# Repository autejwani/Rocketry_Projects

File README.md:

# Rocketry Projects

A collection of my model rocketry projects including flight computer hardware, firmware, ground station software, and certification flight documentation.

---

## Projects

| Project | Status | Current Checkpoint | Description |
|---|---|---|---|
| TALON-1 | In Progress | TALON-1B and 1C complete, TALON-1A schematic in progress | Modular 3-board flight computer system |
| Ground Station | In Progress | 3D orientation view complete, LoRa and GPS support planned | Python telemetry ground station application |
| Flight Computer | Complete | Ground station validation complete | First iteration STM32F411RE flight computer |
| Telemetry | Complete | Validated on STM32F411RE, TALON-1 port planned | C++ telemetry protocol for STM32 |
| LoRa Test | Planned | Not started | LoRa radio range and reliability testing |
| L1 | Complete | Certified March 8 2025 at Higgs Farm | H100 motor, Tripoli L1 certification |
| L2 | In Progress | CAD in progress | J, K, or L class dual deploy certification flight |
| L3 | Planned | Not started | M class or higher dual deploy certification flight |

---

## TALON-1 System Overview

TALON-1 is a modular flight computer built around a 3-board stacking architecture connected via 2.54mm pitch pin headers. Each board serves a dedicated purpose and can be developed and tested independently.

**Base Layer — TALON-1A**
- STM32H503KBU6 microcontroller
- AP63203WU-7 3.3V 2A buck converter
- TB6612FNG dual H-bridge motor driver for airbrake control
- Distributes power and signals to upper boards via stacking headers

**Sensor Layer — TALON-1B**
- IMU: LSM6DSVTR — accelerometer and gyroscope
- Barometer: LPS27HHWTR — pressure and temperature
- Magnetometer: IIS2MDCTR

**Communications Layer — TALON-1C**
- GPS: MAX-M10M-00B
- LoRa: RA-01H — 915 MHz long range telemetry

---

## Flight Computer (First Iteration)

The original flight computer used for development and testing. Built around the STM32F411RE Nucleo development board.

**Sensors**
- IMU: LSM6DSO — accelerometer and gyroscope
- Barometer: LPS22HB — pressure and temperature

This board was used to develop and validate the telemetry protocol, sensor libraries, and ground station application before designing the TALON-1 custom PCB.

---

## Ground Station

A desktop application written in Python that receives and displays live telemetry from any flight computer that implements the TALON-1 packet protocol.

**Features**
- Serial port and baud rate selection
- Live barometer readout — pressure, temperature, altitude
- Live accelerometer and gyroscope readouts
- Flight state display with progress indicator across all flight phases
- 3D rocket orientation visualization driven by live gyroscope data
- Compatible with any future flight computer that implements the telemetry protocol

---

## Telemetry Protocol

All flight computers in this repository share a common binary packet format transmitted over UART at 115200 baud. The protocol is transport independent — the same packet format works over USB serial today and will work over LoRa radio in future revisions.

| Parameter | Value |
|---|---|
| Header bytes | 0x07 0x32 |
| Packet size | 44 bytes |
| Byte order | Little endian |
| Checksum | XOR of all bytes between header and checksum field |
| Data rate | 20 Hz |

Any flight computer that implements this protocol is immediately compatible with the ground station without any changes to the application. See `Telemetry/README.md` for the full packet specification.

---

## Flight Certifications

| Level | Date | Location | Motor | Status |
|---|---|---|---|---|
| L1 | March 8, 2025 | Higgs Farm | H100 | Complete |
| L2 | TBD | TBD | J, K, or L class | In Progress |
| L3 | TBD | TBD | M class or higher | Planned |

---

## Repository Structure
```
Rocketry_Projects/
│
├── TALON-1/              modular flight computer hardware and firmware
├── Ground Station/       Python telemetry ground station application
├── Flight Computer/      first iteration flight computer
├── Telemetry/            shared C++ telemetry protocol
├── LoRa_Test/            LoRa radio testing
├── L1/                   level 1 certification flight
├── L2/                   level 2 certification flight
└── L3/                   level 3 certification flight
```

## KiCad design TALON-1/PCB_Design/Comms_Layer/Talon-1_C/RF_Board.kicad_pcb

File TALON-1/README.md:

# TALON-1 Modular Flight Computer System

TALON-1 is a modular three-board avionics stack designed for high-powered rocketry applications across all certification levels under Tripoli Rocketry Association and National Association of Rocketry guidelines. The system operates in the 915 MHz ISM band for long range telemetry.

---

## Development Checkpoints

| Checkpoint | TALON-1A | TALON-1B | TALON-1C |
|---|---|---|---|
| Component Selection | Complete | Complete | Complete |
| Schematic Design | Complete | Complete | Complete |
| PCB Layout | Complete | Complete | Complete |
| PCB Fabrication | Not Started | Not Started | Not Started |
| Assembly | Not Started | Not Started | Not Started |
| Bring-up Testing | Not Started | Not Started | Not Started |
| Sensor Validation | Not Started | Not Started | Not Started |
| System Integration | Not Started | Not Started | Not Started |
| Flight Testing | Not Started | Not Started | Not Started |

---

## System Overview

The TALON-1 is a three-board modular avionics stack built on a circular PCB form factor. The three modules are designated TALON-1A (Core Processing), TALON-1B (Sensing), and TALON-1C (RF and Navigation), stacked bottom to top and connected via 2.54mm pitch pin headers.

---

## Assembled Stack

*Photo of fully assembled TALON-1 stack (all three boards) to be added here.*

*CAD render of assembled stack to be added here.*

---

## Board Overview

### TALON-1A — Core Processing Module
*PCB image to be added here.*

The base board of the stack. Hosts the STM32H503KBU6 microcontroller running at up to 250 MHz on an ARM Cortex-M33 core, the AP63203WU-7 3.3V 2A buck converter, and the TB6612FNG dual H-bridge motor driver for airbrake control. All inter-board signals originate from this board via male 2.54mm pin headers.

| Item | Detail |
|---|---|
| Microcontroller | STM32H503KBU6 |
| Core | ARM Cortex-M33 @ 250 MHz |
| Flash | 128 KB |
| SRAM | 32 KB |
| Package | UFQFPN-32 |
| Power Regulator | AP63203WU-7 — 3.3V 2A |
| Motor Driver | TB6612FNG — Dual H-Bridge |
| Input Voltage | 3S LiPo (11.1V nominal, 12.6V max) |

---

### TALON-1B — Sensing Module
*PCB image to be added here.*

The middle board of the stack. Carries three ST MEMS sensors on a shared I2C bus. Receives signals from TALON-1A below and passes all signals through to TALON-1C above.

| Sensor | Part | Function | Interface | Address |
|---|---|---|---|---|
| IMU | LSM6DSVTR | 3-axis Accel + 3-axis Gyro | I2C | 0x6A or 0x6B |
| Barometer | LPS27HHWTR | Pressure + Temperature | I2C | 0x5C or 0x5D |
| Magnetometer | IIS2MDCTR | 3-axis Magnetic Field | I2C | 0x1E (fixed) |

I2C pull-up resistors (4.7kΩ) are placed on this board only. No additional pull-ups on TALON-1A or TALON-1C to avoid bus loading.

---

### TALON-1C — RF and Navigation Module
*PCB image to be added here.*

The topmost board of the stack. Hosts the RA-01H 915 MHz LoRa transceiver and the u-blox MAX-M10M GNSS receiver. Being at the top of the stack positions this board closest to any externally mounted antenna, minimising RF feedline losses.

| Device | Part | Function | Interface | Address / Notes |
|---|---|---|---|---|
| LoRa Radio | RA-01H | 915 MHz Telemetry | SPI | CS, DIO1, RESET |
| GNSS | MAX-M10M-00B | GPS, GLONASS, Galileo, BeiDou | I2C | 0x42 (fixed) |

The RA-01H uses a quarter-wave whip antenna at 915 MHz with a wire length of approximately 81.9 mm. The MAX-M10M connects to a separate GNSS antenna via SMA connector.

---

## Inter-Board Bus Pinout

| Signal | Type | Destination |
|---|---|---|
| 3V3 | Power | All boards |
| GND | Power | All boards |
| SDA | I2C Data | TALON-1B sensors, TALON-1C GPS |
| SCL | I2C Clock | TALON-1B sensors, TALON-1C GPS |
| MOSI | SPI Data | TALON-1C RA-01H |
| MISO | SPI Data | TALON-1C RA-01H |
| SCK | SPI Clock | TALON-1C RA-01H |
| CS | SPI Chip Select | TALON-1C RA-01H |
| DIO1 | Digital Input | TALON-1C RA-01H interrupt |
| RESET | Digital Output | TALON-1C RA-01H reset |

---

## Power Architecture

The entire stack is powered by a single 3S LiPo battery (11.1V nominal, 12.6V fully charged). The AP63203WU-7 buck converter on TALON-1A regulates this down to 3.3V for all digital logic and sensors across the stack. Raw battery voltage is fed directly to the TB6612FNG motor driver for airbrake motor control.

---

## Firmware

Firmware targets the STM32H503KBU6 using the STM32 HAL library via PlatformIO. Development is ongoing and will cover sensor acquisition, flight state machine logic, telemetry transmission over LoRa, and GNSS data parsing. See the `Code/` folder for current firmware.

---

## Repository Structure
```
TALON-1/
│
├── PCB Design/
│   ├── Base Layer/        TALON-1A KiCad files
│   ├── Sensor Layer/      TALON-1B KiCad files
│   └── Comms Layer/       TALON-1C KiCad files
│
├── CAD/                   mechanical CAD files
├── Code/                  PlatformIO firmware project
│
└── Docs/
    ├── architecture.md
    ├── packet_protocol.md
    └── board_pinout.md
```

---

## Design Philosophy

TALON-1 was designed with an emphasis on modularity, repairability, and iterative development. Separating processing, sensing, and RF functions into discrete modules means a change to one layer does not require a redesign of the others. Each board can be developed, tested, and replaced independently.

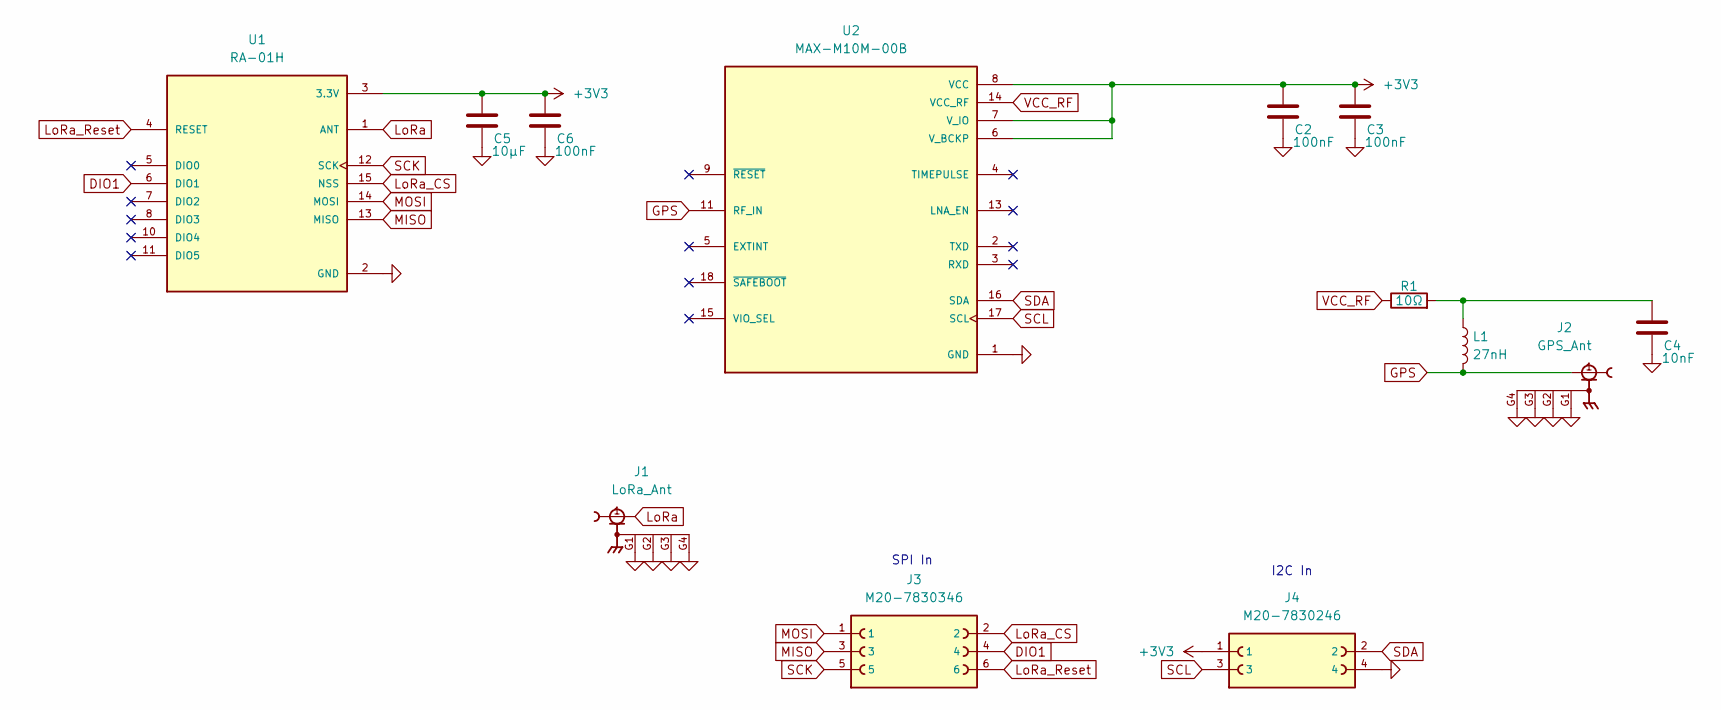
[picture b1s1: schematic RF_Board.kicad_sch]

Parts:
C2, C3, C6: 100nF; C_0805_2012Metric
C4: 10nF; C_0805_2012Metric
C5: 10µF; C_0805_2012Metric
J1: LoRa_Ant; GRADCONN_RFPC-SMA28-F; PARTREV 1.0; DigiKey_Part_Number 2073-RFPC-SMA28-F-ND
J2: GPS_Ant; GRADCONN_RFPC-SMA28-F; PARTREV 1.0; DigiKey_Part_Number 2073-RFPC-SMA28-F-ND
J3: M20-7830346; HARWIN_M20-7830346; DigiKey_Part_Number 952-1781-ND
J4: M20-7830246; HARWIN_M20-7830246; PARTREV 13; DigiKey_Part_Number 952-2147-ND
L1: 27nH; L_0805_2012Metric
R1: 10Ω; R_0603_1608Metric
U1: RA-01H; XCVR_RA-01H; PARTREV V1.0
U2: MAX-M10M-00B; XCVR_MAX-M10M-00B; PARTREV C1; DigiKey_Part_Number 672-MAX-M10M-00BCT-ND

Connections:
+3V3: C2.1, C3.1, C5.1, C6.1, J4.1, U1.3 (3.3V), U2.6 (V_BCKP), U2.7 (V_IO), U2.8 (VCC)
DIO1: J3.4, U1.6 (DIO1)
GND: C2.2, C3.2, C4.2, C5.2, C6.2, J1.G1, J1.G2, J1.G3, J1.G4, J2.G1, J2.G2, J2.G3, J2.G4, J4.4, U1.2 (GND), U1.9 (GND), U1.16 (GND), U2.1 (GND), U2.10 (GND), U2.12 (GND)
GPS: J2.1, L1.2, U2.11 (RF_IN)
LoRa: J1.1, U1.1 (ANT)
LoRa_CS: J3.2, U1.15 (NSS)
LoRa_Reset: J3.6, U1.4 (RESET)
MISO: J3.3, U1.13 (MISO)
MOSI: J3.1, U1.14 (MOSI)
unnamed: C4.1, L1.1, R1.2
SCK: J3.5, U1.12 (SCK)
SCL: J4.3, U2.17 (SCL)
SDA: J4.2, U2.16 (SDA)
VCC_RF: R1.1, U2.14 (VCC_RF)

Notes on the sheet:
SPI In
I2C In

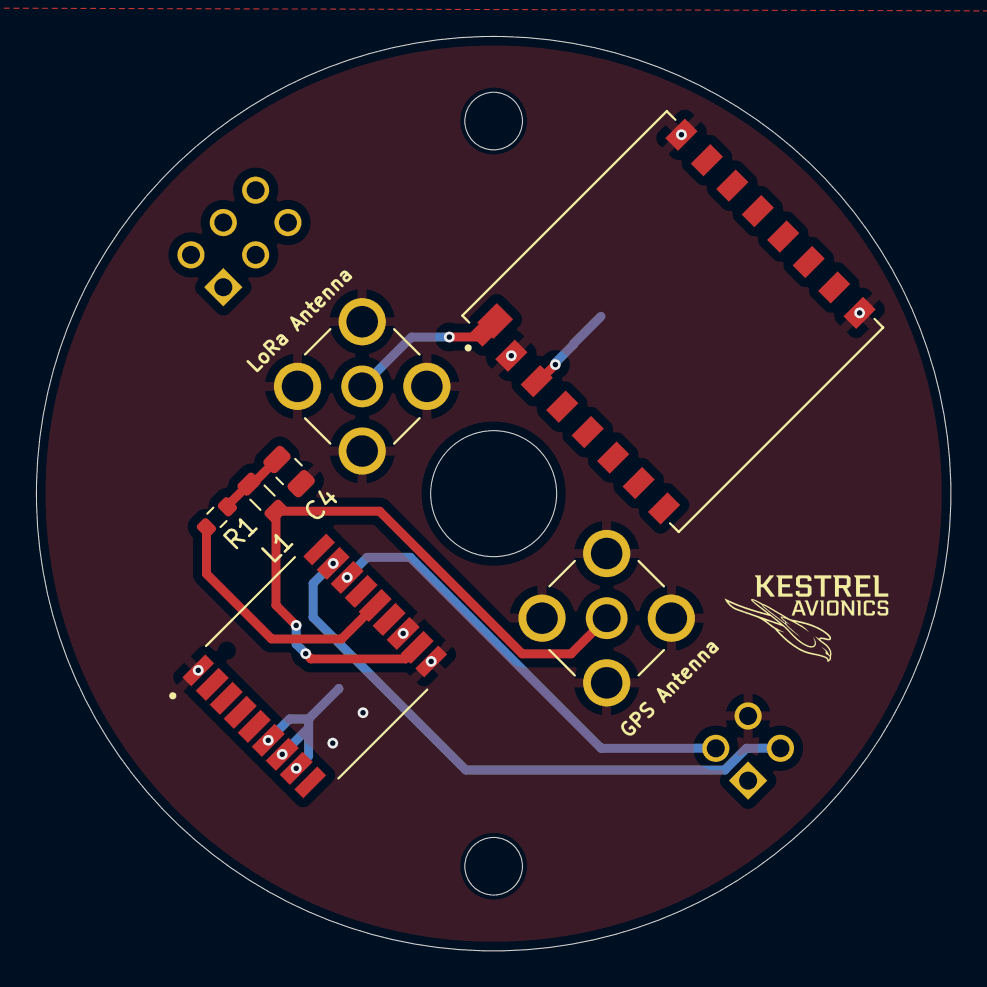
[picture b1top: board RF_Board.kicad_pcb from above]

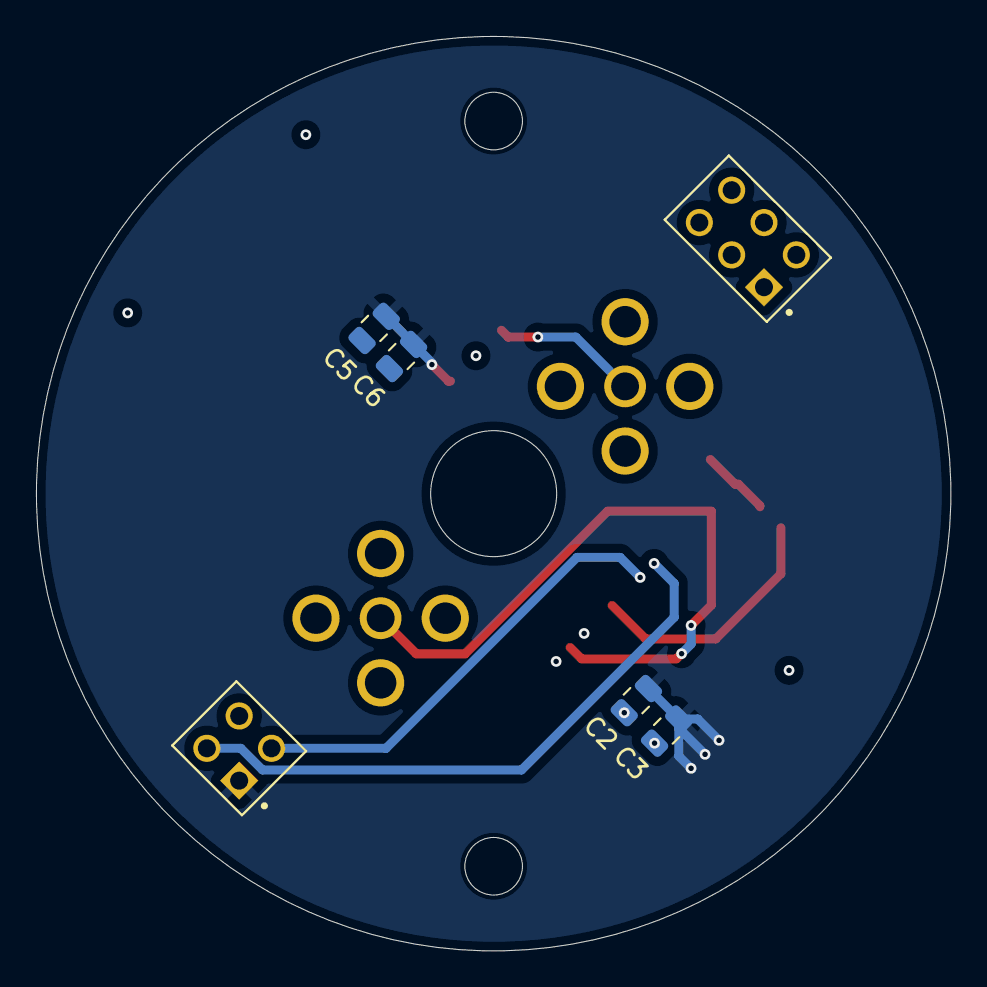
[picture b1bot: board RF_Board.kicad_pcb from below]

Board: 2 copper layers, 50.8 x 50.8 mm, 13 parts (6 on the bottom side), 14 nets.

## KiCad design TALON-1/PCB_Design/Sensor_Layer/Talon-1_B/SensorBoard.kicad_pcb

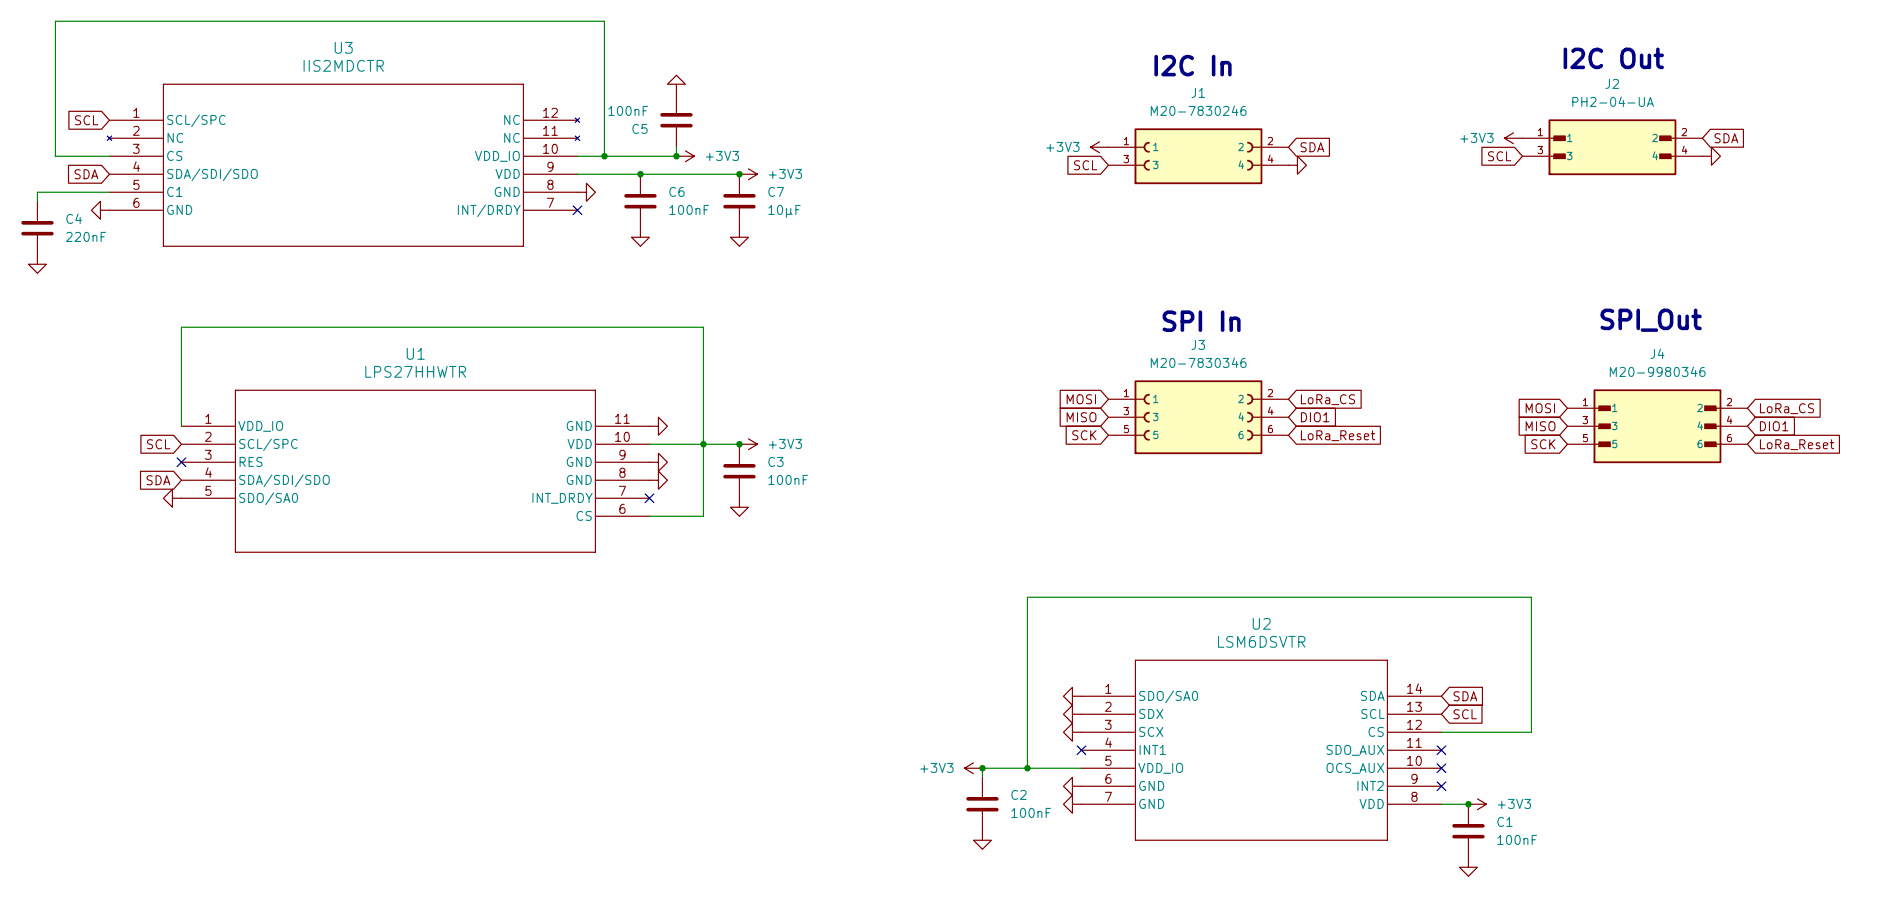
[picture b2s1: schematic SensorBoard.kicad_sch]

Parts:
C1, C2, C3, C5, C6: 100nF; C_0805_2012Metric
C4: 220nF; C_0805_2012Metric
C7: 10μF; C_0805_2012Metric
J1: M20-7830246; HARWIN_M20-7830246; PARTREV 13; DigiKey_Part_Number 952-2147-ND
J2: PH2-04-UA; ADAM_PH2-04-UA; DigiKey_Part_Number 2057-PH2-04-UA-ND
J3: M20-7830346; HARWIN_M20-7830346; DigiKey_Part_Number 952-1781-ND
J4: M20-9980346; HARWIN_M20-9980346; DigiKey_Part_Number 952-2121-ND
U1: LPS27HHWTR; QFN_HHWTR_STM
U2: LSM6DSVTR; LGA14-L_2P59X3P1X0P5_STM
U3: IIS2MDCTR; LGA-12_2X2X0P7_STM

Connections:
+3V3: C1.1, C2.1, C3.1, C5.1, C6.1, C7.1, J1.1, J2.1, U1.1 (VDD_IO), U1.6 (CS), U1.10 (VDD), U2.5 (VDD_IO), U2.8 (VDD), U2.12 (CS), U3.3 (CS), U3.9 (VDD), U3.10 (VDD_IO)
DIO1: J3.4, J4.4
GND: C1.2, C2.2, C3.2, C4.2, C5.2, C6.2, C7.2, J1.4, J2.4, U1.5 (SDO/SA0), U1.8 (GND), U1.9 (GND), U1.11 (GND), U2.1 (SDO/SA0), U2.2 (SDX), U2.3 (SCX), U2.6 (GND), U2.7 (GND), U3.6 (GND), U3.8 (GND)
LoRa_CS: J3.2, J4.2
LoRa_Reset: J3.6, J4.6
MISO: J3.3, J4.3
MOSI: J3.1, J4.1
unnamed: C4.1, U3.5 (C1)
SCK: J3.5, J4.5
SCL: J1.3, J2.3, U1.2 (SCL/SPC), U2.13 (SCL), U3.1 (SCL/SPC)
SDA: J1.2, J2.2, U1.4 (SDA/SDI/SDO), U2.14 (SDA), U3.4 (SDA/SDI/SDO)

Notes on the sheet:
SPI In
I2C In
SPI_Out
I2C Out

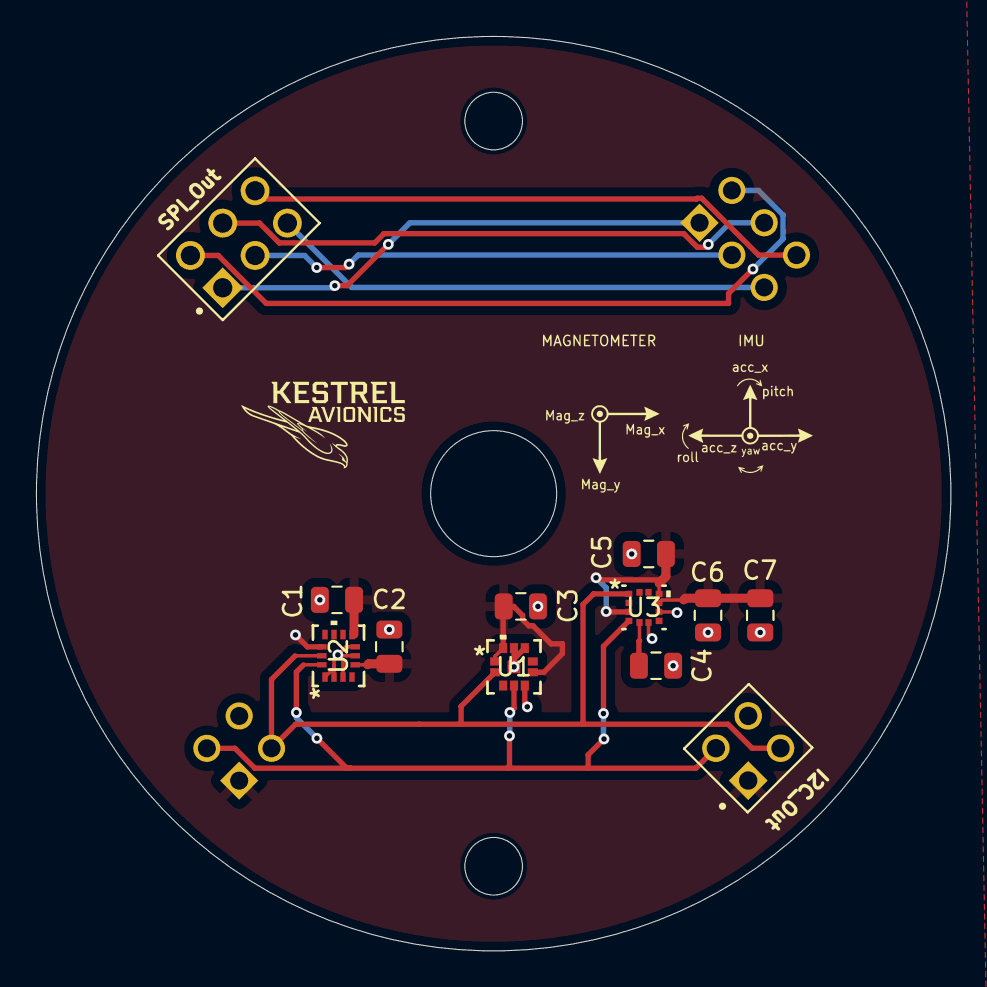
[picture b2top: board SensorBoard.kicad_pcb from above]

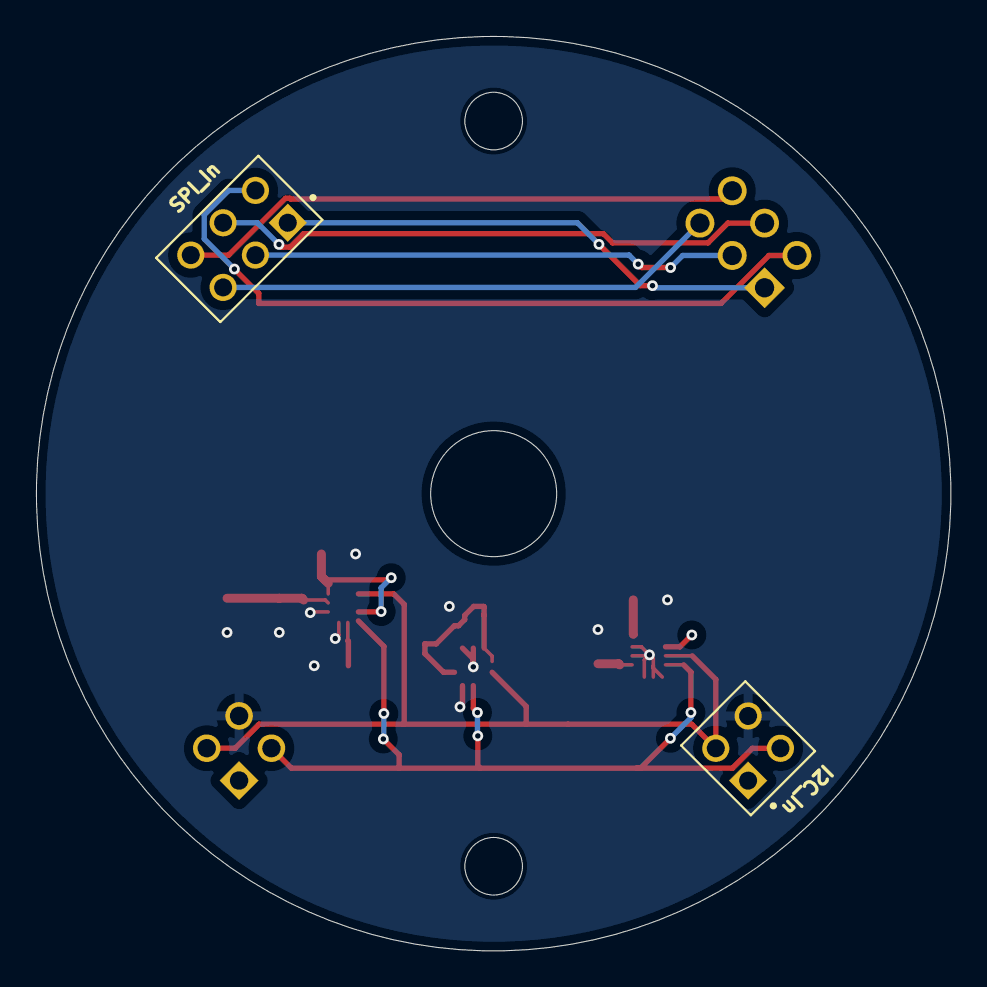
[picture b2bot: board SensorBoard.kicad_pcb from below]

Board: 2 copper layers, 50.8 x 50.8 mm, 14 parts (2 on the bottom side), 11 nets.

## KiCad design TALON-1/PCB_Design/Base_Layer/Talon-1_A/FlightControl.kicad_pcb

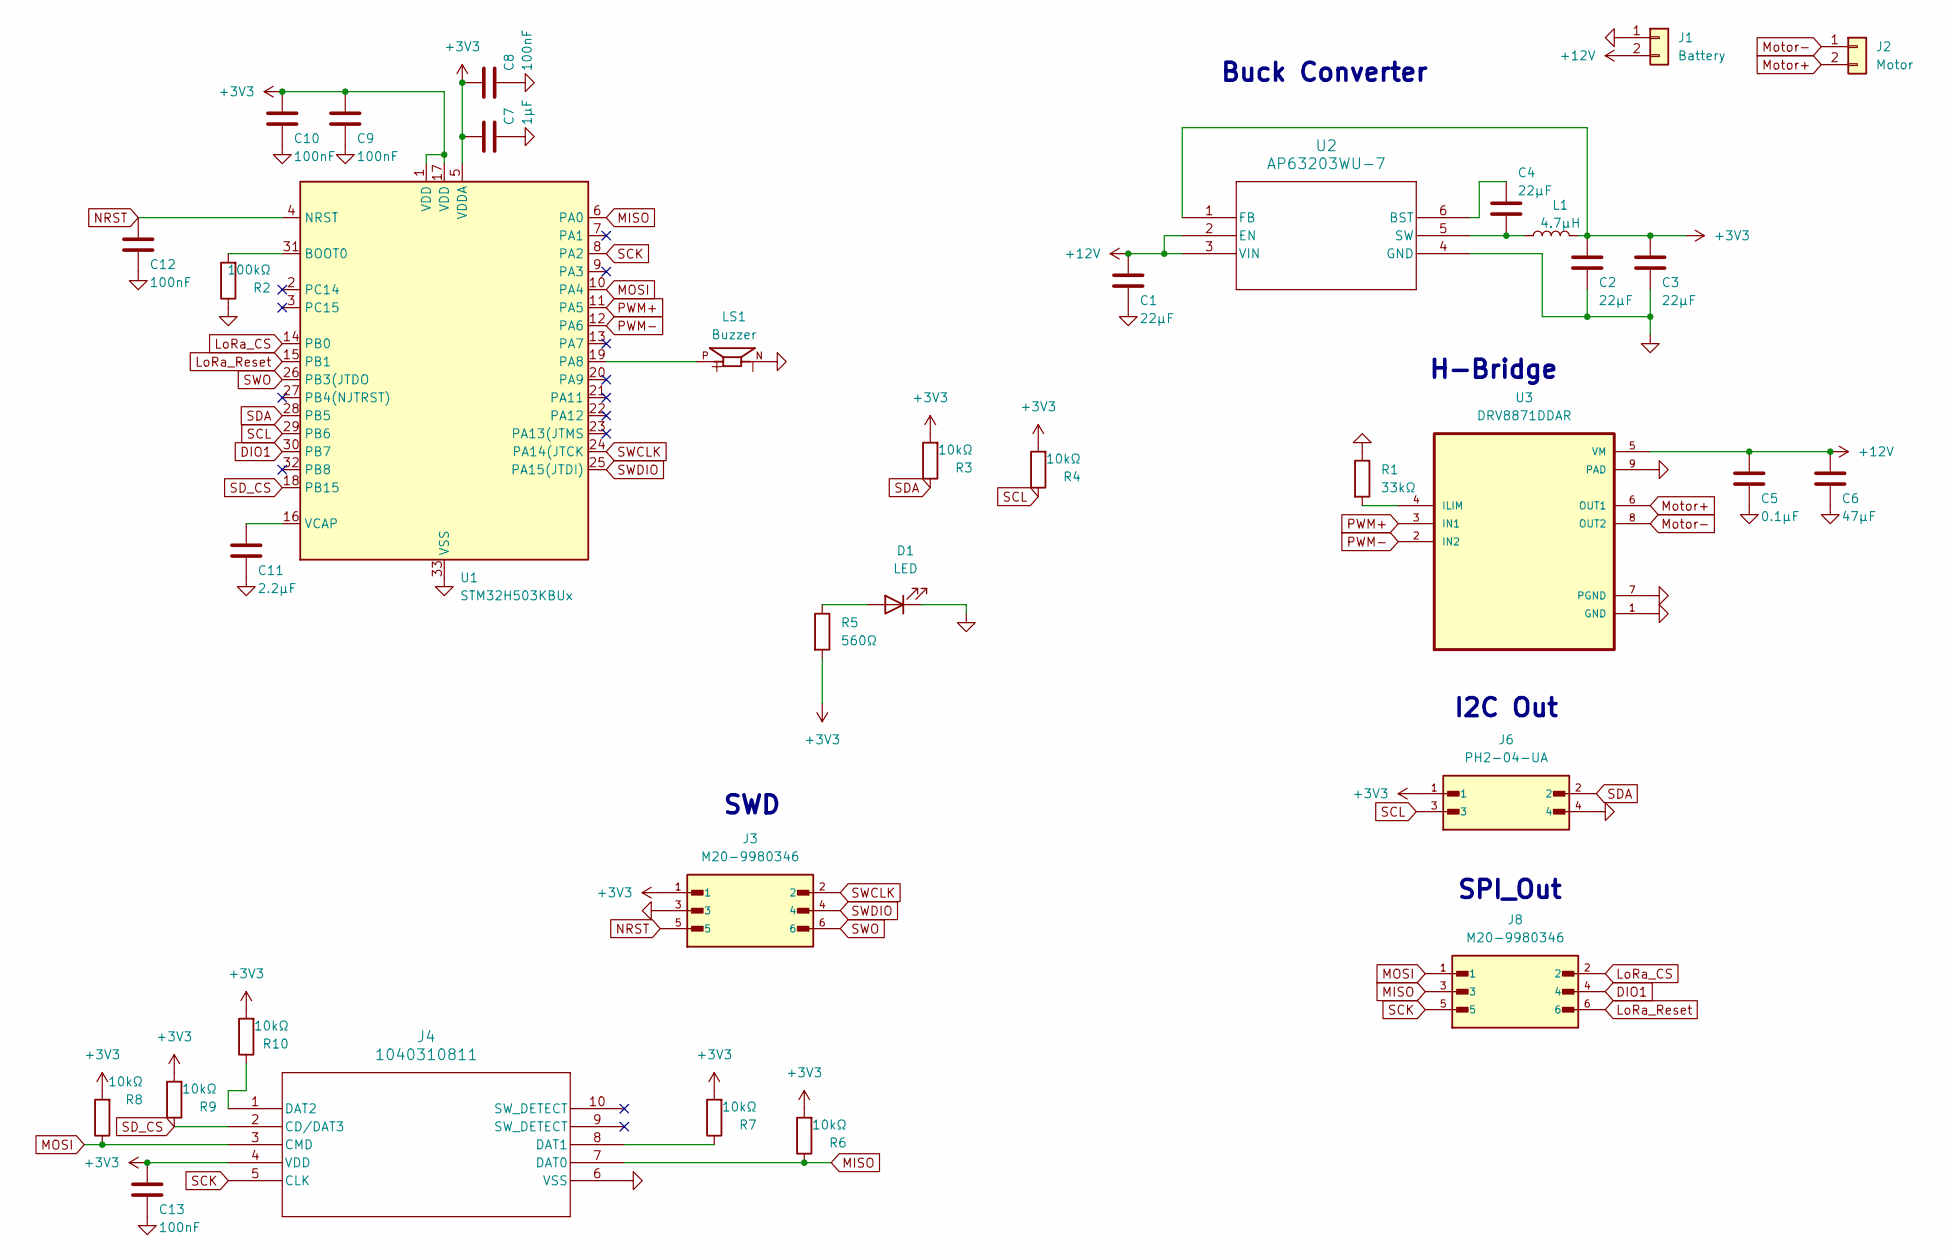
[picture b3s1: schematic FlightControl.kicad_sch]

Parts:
C1, C2, C3, C4: 22μF; C_0805_2012Metric
C5: 0.1μF; C_0805_2012Metric
C6: 47μF; C_0805_2012Metric
C7: 1μF; C_0805_2012Metric
C8, C9, C10, C12, C13: 100nF; C_0805_2012Metric
C11: 2.2μF; C_0805_2012Metric
D1: LED; LED_0805_2012Metric
J1: Battery; TerminalBlock_Phoenix_MKDS-1,5-2_1x02_P5.00mm_Horizontal
J2: Motor; TerminalBlock_Phoenix_MKDS-1,5-2_1x02_P5.00mm_Horizontal
J3, J8: M20-9980346; HARWIN_M20-9980346; DigiKey_Part_Number 952-2121-ND
J4: 1040310811; 104031-0811_MOL
J6: PH2-04-UA; ADAM_PH2-04-UA; DigiKey_Part_Number 2057-PH2-04-UA-ND
L1: 4.7μH; LED_0603_1608Metric
LS1: Buzzer; CUI_CMT-8540S-SMT; DigiKey_Part_Number 102-3746-1-ND
R1: 33kΩ; R_0603_1608Metric
R2: 100kΩ; R_0603_1608Metric
R3, R4, R6, R7, R8, R9, R10: 10kΩ; R_0603_1608Metric
R5: 560Ω; R_0603_1608Metric
U1: STM32H503KBUx; QFN-32-1EP_5x5mm_P0.5mm_EP3.45x3.45mm
U2: AP63203WU-7; AP63203WU-7_DIO
U3: DRV8871DDAR; VREG_LM5017MR_NOPB; DigiKey_Part_Number 296-43024-1-ND

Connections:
+3V3: C2.1, C3.1, C7.1, C8.1, C9.1, C10.1, C13.1, J3.1, J4.4 (VDD), J6.1, L1.2, R3.2, R4.2, R5.2, R6.2, R7.2, R8.2, R9.2, R10.2, U1.1 (VDD), U1.5 (VDDA), U1.17 (VDD), U2.1 (FB)
+12V: C1.1, C5.1, C6.1, J1.2, U2.2 (EN), U2.3 (VIN), U3.5 (VM)
DIO1: J8.4, U1.30 (PB7)
GND: C1.2, C2.2, C3.2, C5.2, C6.2, C7.2, C8.2, C9.2, C10.2, C11.2, C12.2, C13.2, D1.1 (K), J1.1, J3.3, J4.6 (VSS), J4.11, J4.12, J4.13, J4.14, J6.4, LS1.N, R1.1, R2.1, U1.33 (VSS), U2.4 (GND), U3.1 (GND), U3.7 (PGND), U3.9 (PAD), U3.10, U3.11, U3.12, U3.13, U3.14, U3.15, U3.16, U3.17
LoRa_CS: J8.2, U1.14 (PB0)
LoRa_Reset: J8.6, U1.15 (PB1)
MISO: J4.7 (DAT0), J8.3, R6.1, U1.6 (PA0)
MOSI: J4.3 (CMD), J8.1, R8.1, U1.10 (PA4)
Motor+: J2.2, U3.6 (OUT1)
Motor-: J2.1, U3.8 (OUT2)
NRST: C12.1, J3.5, U1.4 (NRST)
unnamed: D1.2 (A), R5.1
unnamed: J4.8 (DAT1), R7.1
unnamed: J4.1 (DAT2), R10.1
unnamed: R2.2, U1.31 (BOOT0)
unnamed: LS1.P, U1.19 (PA8)
unnamed: C11.1, U1.16 (VCAP)
unnamed: C4.1, U2.6 (BST)
unnamed: C4.2, L1.1, U2.5 (SW)
unnamed: R1.2, U3.4 (ILIM)
PWM+: U1.11 (PA5), U3.3 (IN1)
PWM-: U1.12 (PA6), U3.2 (IN2)
SCK: J4.5 (CLK), J8.5, U1.8 (PA2)
SCL: J6.3, R4.1, U1.29 (PB6)
SDA: J6.2, R3.1, U1.28 (PB5)
SD_CS: J4.2 (CD/DAT3), R9.1, U1.18 (PB15)
SWCLK: J3.2, U1.24 (PA14(JTCK)
SWDIO: J3.4, U1.25 (PA15(JTDI))
SWO: J3.6, U1.26 (PB3(JTDO)

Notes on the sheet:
H-Bridge
I2C Out
Buck Converter
SWD
SPI_Out

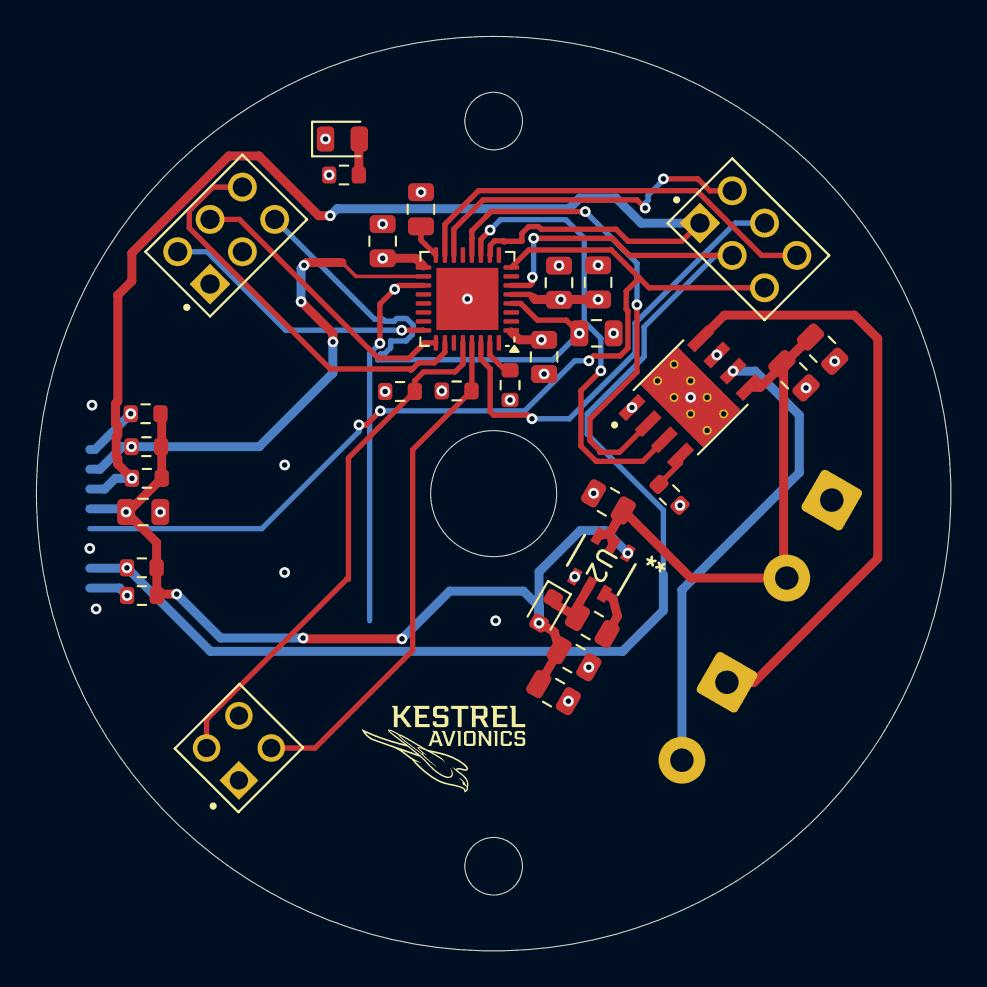
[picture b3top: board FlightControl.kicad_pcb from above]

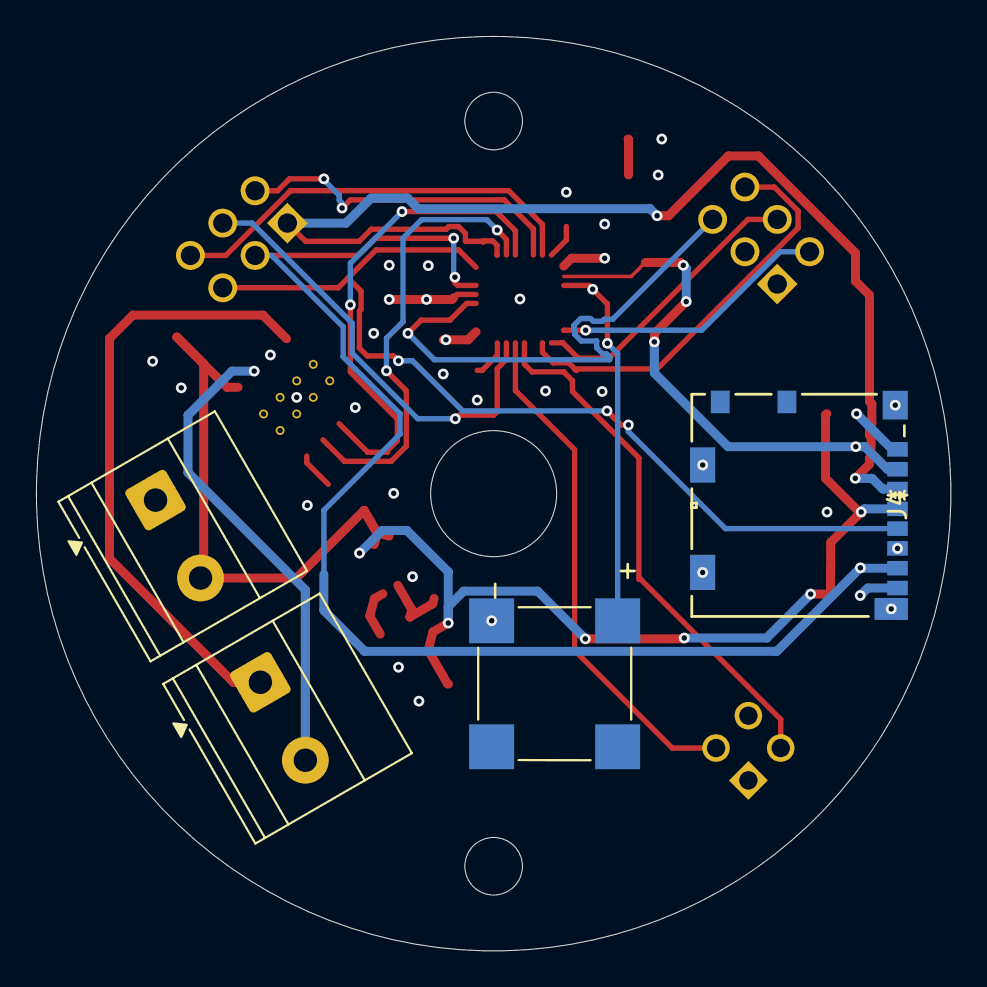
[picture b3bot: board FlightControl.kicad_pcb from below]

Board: 4 copper layers, 50.8 x 50.8 mm, 35 parts (4 on the bottom side), 29 nets.

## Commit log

2026-03-22 Add Project Structure
2026-03-22 updated folders
2026-03-22 hello
2026-03-23 Update files
